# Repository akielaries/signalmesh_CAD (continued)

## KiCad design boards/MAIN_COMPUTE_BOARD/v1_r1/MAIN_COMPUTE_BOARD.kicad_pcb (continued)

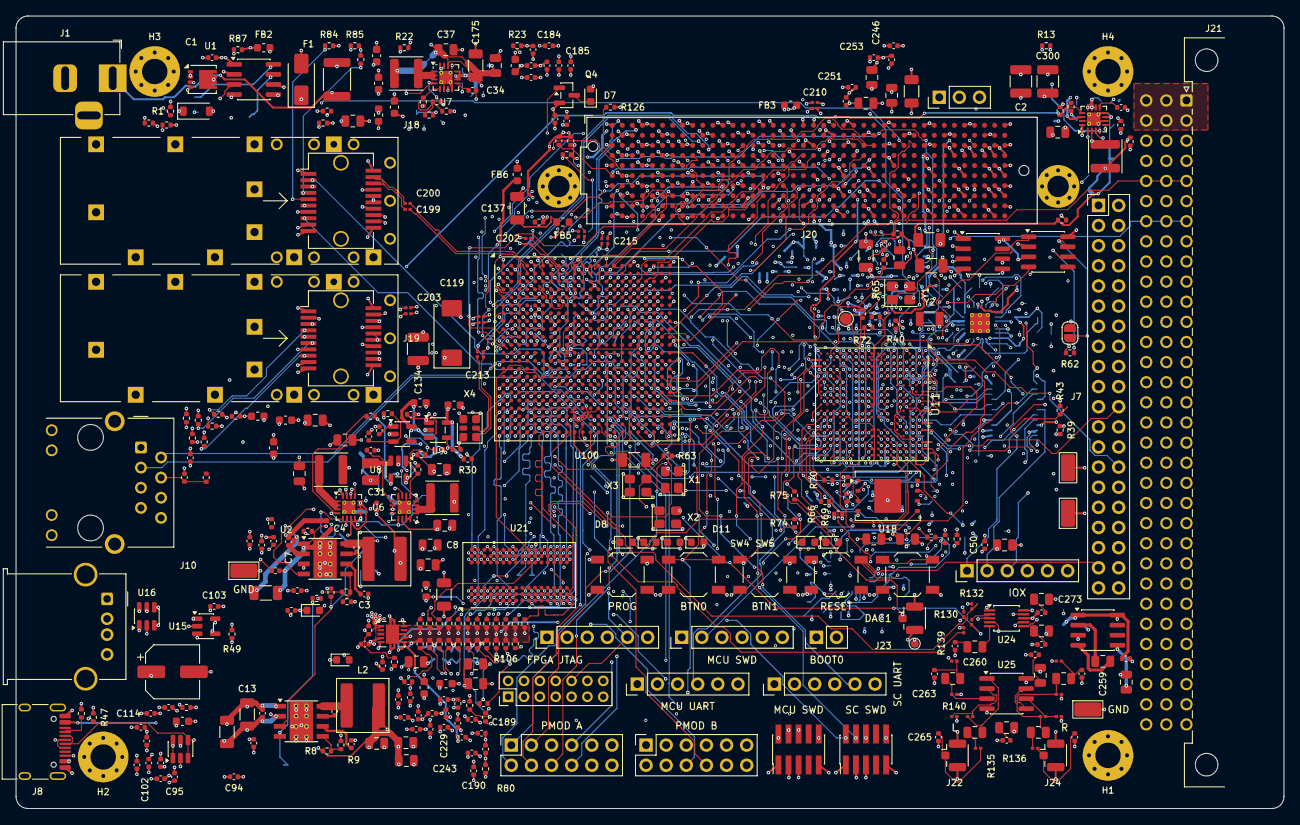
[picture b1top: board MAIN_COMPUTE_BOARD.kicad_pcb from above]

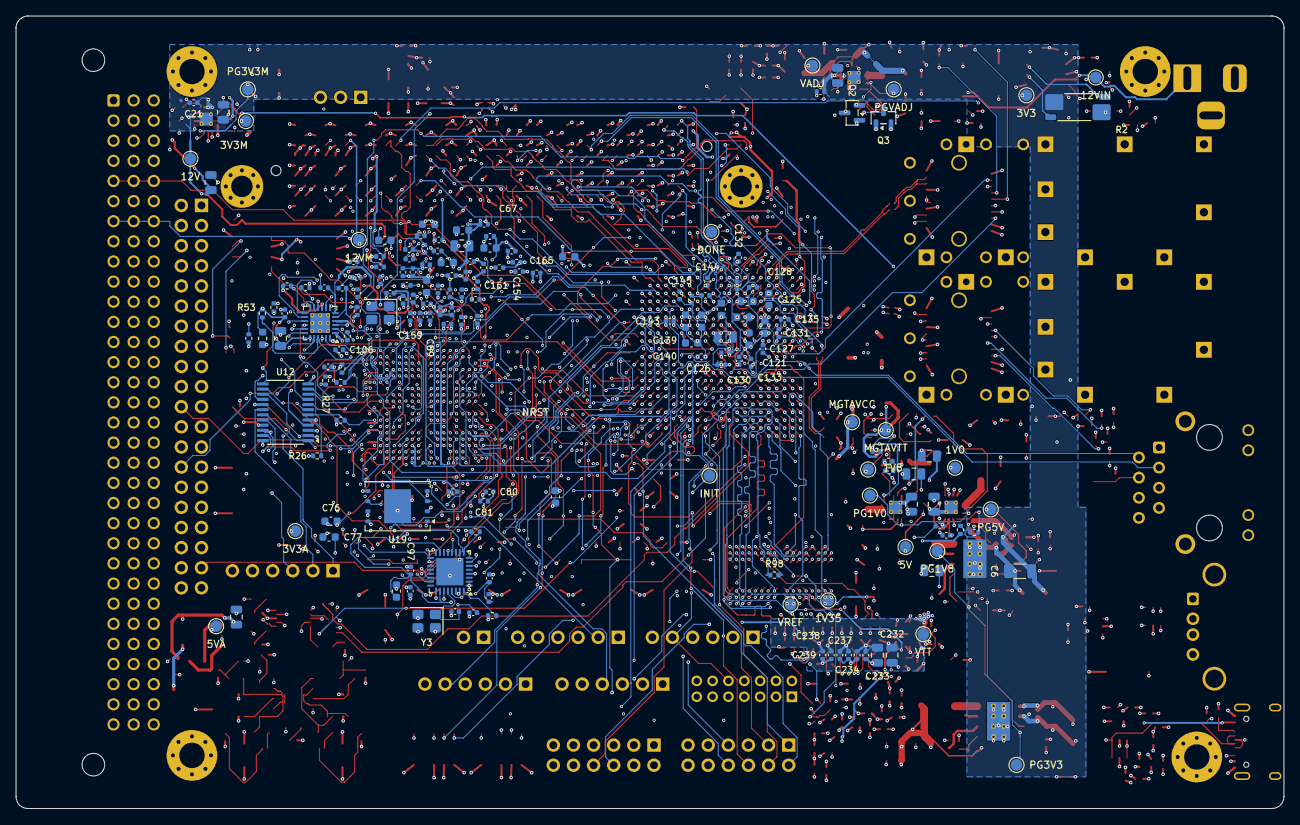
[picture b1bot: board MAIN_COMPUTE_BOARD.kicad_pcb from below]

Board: 10 copper layers, 160.0 x 100.0 mm, 547 parts (173 on the bottom side), 492 nets.

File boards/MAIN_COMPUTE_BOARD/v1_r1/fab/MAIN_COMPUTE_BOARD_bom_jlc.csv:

Comment,Designator,Footprint,LCSC Part #
100nF,"C1,C4,C12,C48,C50,C52-C72,C79,C81,C87-C89,C92-C95,C97,C98,C100,C110-C114,C116,C118,C148,C188-C190,C194,C195,C197,C198,C211,C217,C219,C222-C231,C234-C240,C242,C243,C246,C247,C250,C251",C_0402_1005Metric,
22uF 25V X5R,"C2,C300",C_1210_3225Metric,
1uF,"C3,C11,C42,C44,C45,C78,C80,C101-C103,C107,C115,C117,C241",C_0402_1005Metric,
10uF 25V,"C5,C6,C13,C14",C_1206_3216Metric,
100nF 25V,"C7,C15,C21,C26,C31,C36,C253",C_0402_1005Metric,
22uF,"C8-C10,C16-C18,C22,C23,C27,C28,C32,C33,C37,C38,C40,C41,C216,C218",C_0805_2012Metric,
3.3nF,"C19,C24,C29,C34",C_0402_1005Metric,
10uF 25V,"C20,C25,C30,C35,C51,C252",C_0805_2012Metric,
10uF,"C39,C47,C49,C75,C109,C147,C191,C192,C220,C221,C232,C233,C245,C249,C255-C260,C263,C266,C270,C273",C_0805_2012Metric,
4.7uF,"C43,C46,C73,C74,C96,C99,C120-C125,C138-C140,C150,C151,C156,C157,C162,C163,C169,C170,C176,C177,C182,C183,C193,C196",C_0603_1608Metric,
2.2uF,"C76,C77",C_0603_1608Metric,
10nF,C82,C_0402_1005Metric,
10pF,"C83,C84",C_0402_1005Metric,
8.2pF,"C85,C86",C_0402_1005Metric,
18pF,"C90,C91",C_0402_1005Metric,
100uF 10V,C104,CP_Elec_6.3x7.7,
15pF,"C105,C106",C_0402_1005Metric,
470pF,C108,C_0402_1005Metric,
330uF 2.5V polymer,C119,CP_EIA-7343-31_Kemet-D,
470nF,"C126-C133,C135,C136,C141-C145,C152-C155,C158-C161,C164-C167,C171-C174,C178-C181,C184-C187",C_0402_1005Metric,
100uF,C134,C_1210_3225Metric,
47uF,"C137,C146,C149,C168,C175,C244,C248",C_1206_3216Metric,
100nF,"C199-C210,C212-C215",C_0201_0603Metric,
0.1uF,"C254,C264,C268,C269,C272",C_0402_1005Metric,
2.7nF,"C261,C271",C_0402_1005Metric,
47pF,"C262,C265",C_0402_1005Metric,
100uF,C267,C_0805_2012Metric,
SMAJ15A,D1,D_SMA,
BZT52C10,D2,D_SOD-123,
RED 12V,D3,LED_0603_1608Metric,
GREEN 3V3,D4,LED_0603_1608Metric,
GREEN,"D5,D8-D11",LED_0603_1608Metric,
BLUE,D6,LED_0603_1608Metric,
GREEN DONE,D7,LED_0603_1608Metric,
3A hold 1812,F1,Fuse_1812_4532Metric,
1.1A hold 1206,F2,Fuse_1206_3216Metric,
600R@100MHz,FB1-FB8,L_0603_1608Metric,
12V IN 5.5x2.1,J1,BarrelJack_Horizontal,
BOOT0,J2,PinHeader_1x02_P2.54mm_Vertical,
MCU_SWD MIPI-10,J3,PinHeader_2x05_P1.27mm_Vertical_SMD,
MCU_SWD,J4,PinHeader_1x06_P2.54mm_Vertical,
MCU_UART FTDI,J5,PinHeader_1x06_P2.54mm_Vertical,
IOX_SPARE,J6,PinHeader_1x06_P2.54mm_Vertical,
MCU_BREAKOUT,J7,PinHeader_2x20_P2.54mm_Vertical,
USB-C HS,J8,USB_C_Receptacle_HRO_TYPE-C-31-M-12,
USB-A HOST MIDI,J9,USB_A_Molex_67643_Horizontal,
HR911105A,J10,RJ45_Hanrun_HR911105A_Horizontal,
CAN,J11,PinHeader_1x03_P2.54mm_Vertical,
FPGA_JTAG Xilinx,J12,PinHeader_2x07_P2.00mm_Vertical,
FPGA_JTAG 6p,J13,PinHeader_1x06_P2.54mm_Vertical,
SOFTCORE_SWD MIPI-10,J14,PinHeader_2x05_P1.27mm_Vertical_SMD,
SOFTCORE_UART FTDI,J15,PinHeader_1x06_P2.54mm_Vertical,
PMODA,J16,PinSocket_2x06_P2.54mm_Vertical,
PMODB,J17,PinSocket_2x06_P2.54mm_Vertical,
SFP cage,"J18,J19",Connector_SFP_and_Cage,
VITA57.1 HPC ASP-134486-01,J20,Samtec_FMC_ASP-134486-01_10x40_P1.27mm_Vertical,
DIN41612 C 3x32 BACKPLANE,J21,DIN41612_C_3x32_Male_Horizontal_THT,
ACM_DAC_L,J22,U.FL_Hirose_U.FL-R-SMT-1_Vertical,
DAC_L_PRB,J23,U.FL_Hirose_U.FL-R-SMT-1_Vertical,
ACM_DAC_R,J24,U.FL_Hirose_U.FL-R-SMT-1_Vertical,
6.8uH 6A,"L1,L2",L_Bourns_SRP6060FA,
2.2uH 4A,L3-L6,L_APV_ANR4020,
2.2uH 1.5A,L7,L_1008_2520Metric,
DMP3013SFV,Q1,Diodes_PowerDI3333-8,
2N7002,Q2-Q4,SOT-23,
10k,"R1,R22,R35,R37,R40,R43,R44,R48,R50-R53,R61,R72,R78-R80,R87,R88,R94,R95,R97,R124,R125",R_0402_1005Metric,
10m 1W,R2,R_Shunt_Vishay_WSK2512_6332Metric_T1.19mm,
100k,"R3,R5,R7,R8,R10,R12,R13,R16,R19,R23,R26,R27,R32,R49,R126",R_0402_1005Metric,
15k,R4,R_0402_1005Metric,
24.9k,R6,R_0402_1005Metric,
43.2k,R9,R_0402_1005Metric,
309k,R11,R_0402_1005Metric,
49.9k,R14,R_0402_1005Metric,
200k,"R15,R18,R21",R_0402_1005Metric,
249k,"R17,R20,R25",R_0402_1005Metric,
280k,R24,R_0402_1005Metric,
150k,R28,R_0402_1005Metric,
120k,R29,R_0402_1005Metric,
90.9k,R30,R_0402_1005Metric,
110k,"R31,R34",R_0402_1005Metric,
130k,R33,R_0402_1005Metric,
1k,"R36,R38,R39,R63-R65,R71,R73-R77",R_0402_1005Metric,
2.2k,"R41,R42",R_0402_1005Metric,
12k 1%,R45,R_0402_1005Metric,
5.1k,"R46,R47",R_0402_1005Metric,
1.5k,R54,R_0402_1005Metric,
12.1k 1%,R55,R_0402_1005Metric,
49.9 1%,R56-R59,R_0402_1005Metric,
0,R60,R_0402_1005Metric,
120,R62,R_0402_1005Metric,
4.7k,"R66,R67,R69,R70,R82-R86,R89-R93",R_0402_1005Metric,
330,R68,R_0402_1005Metric,
100 1%,"R81,R98",R_0402_1005Metric,
240 1%,R96,R_0402_1005Metric,
39.2 1%,R99-R121,R_0402_1005Metric,
10k 1%,"R122,R123",R_0402_1005Metric,
1k,"R127,R137",R_0201_0603Metric,
47k,"R128,R131",R_0201_0603Metric,
22,"R129,R130,R132,R138",R_0201_0603Metric,
2k,"R133,R140",R_0201_0603Metric,
560,"R134,R139",R_0201_0603Metric,
100,"R135,R136",R_0201_0603Metric,
MCU_RESET,SW1,SW_SPST_TL3342,
MCU_USER,SW2,SW_SPST_TL3342,
FPGA_PROG,SW3,SW_SPST_TL3342,
FPGA_BTN0,SW4,SW_SPST_TL3342,
FPGA_BTN1,SW5,SW_SPST_TL3342,
TP GND,TP21-TP24,TestPoint_Keystone_5015_Micro_Mini,
INA219 0x40,U1,SOIC-8_3.9x4.9mm_P1.27mm,
LMR33630ADDA,"U2,U3",Texas_HSOP-8-1EP_3.9x4.9mm_P1.27mm_ThermalVias,
TPS62130RGT,U4-U7,VQFN-16-1EP_3x3mm_P0.5mm_EP1.68x1.68mm_ThermalVias,
TLV62568DBV,U8,SOT-23-5,
TLV75801 MGTAVCC 1V0,U9,SOT-23-5,
TLV75801 MGTAVTT 1V2,U10,SOT-23-5,
STM32H755XIH6,U11,TFBGA-265_14x14mm_Layout17x17_P0.8mm,
TCA9535PWR 0x20,U12,TSSOP-24_4.4x7.8mm_P0.65mm,
USB3300-EZK,U13,QFN-32-1EP_5x5mm_P0.5mm_EP3.45x3.45mm,
USBLC6-2SC6,"U14,U16",SOT-23-6,
TPS2051C,U15,SOT-23-5,
LAN8742A-CZ,U17,VQFN-24-1EP_4x4mm_P0.5mm_EP2.5x2.5mm_ThermalVias,
W25Q01JVZEIQ,"U18,U19",WSON-8-1EP_8x6mm_P1.27mm_EP3.4x4.3mm,C6926235
SN65HVD230,U20,SOIC-8_3.9x4.9mm_P1.27mm,
MT41K256M16TW-107,U21,Micron_FBGA-96_8x14mm_Layout9x16_P0.8mm,
TPS51200DRC,U22,VSON-10-1EP_3x3mm_P0.5mm_EP1.65x2.4mm,
LM2662M,U23,SOIC-8_3.9x4.9mm_P1.27mm,
CS4344,U24,TSSOP-10_3x3mm_P0.5mm,
OPA1656ID,U25,SOIC-8_3.9x4.9mm_P1.27mm,
XC7A100T-2FGG484I,U100,Xilinx_FGG484,
24AA025E48 0x54 MAC,U200,SOIC-8_3.9x4.9mm_P1.27mm,
100MHz 3V3 CMOS,X1,Oscillator_SMD_Abracon_ASE-4Pin_3.2x2.5mm,
24.576MHz 3V3 CMOS,X2,Oscillator_SMD_Abracon_ASE-4Pin_3.2x2.5mm,
22.5792MHz 3V3 CMOS,X3,Oscillator_SMD_Abracon_ASE-4Pin_3.2x2.5mm,
125MHz LVDS,X4,Oscillator_SMD_SiTime_PQFD-6L_3.2x2.5mm,
25MHz 8pF,Y1,Crystal_SMD_3225-4Pin_3.2x2.5mm,
32.768kHz 6pF,Y2,Crystal_SMD_3215-2Pin_3.2x1.5mm,
24MHz 12pF,Y3,Crystal_SMD_3225-4Pin_3.2x2.5mm,
25MHz 10pF,Y4,Crystal_SMD_3225-4Pin_3.2x2.5mm,

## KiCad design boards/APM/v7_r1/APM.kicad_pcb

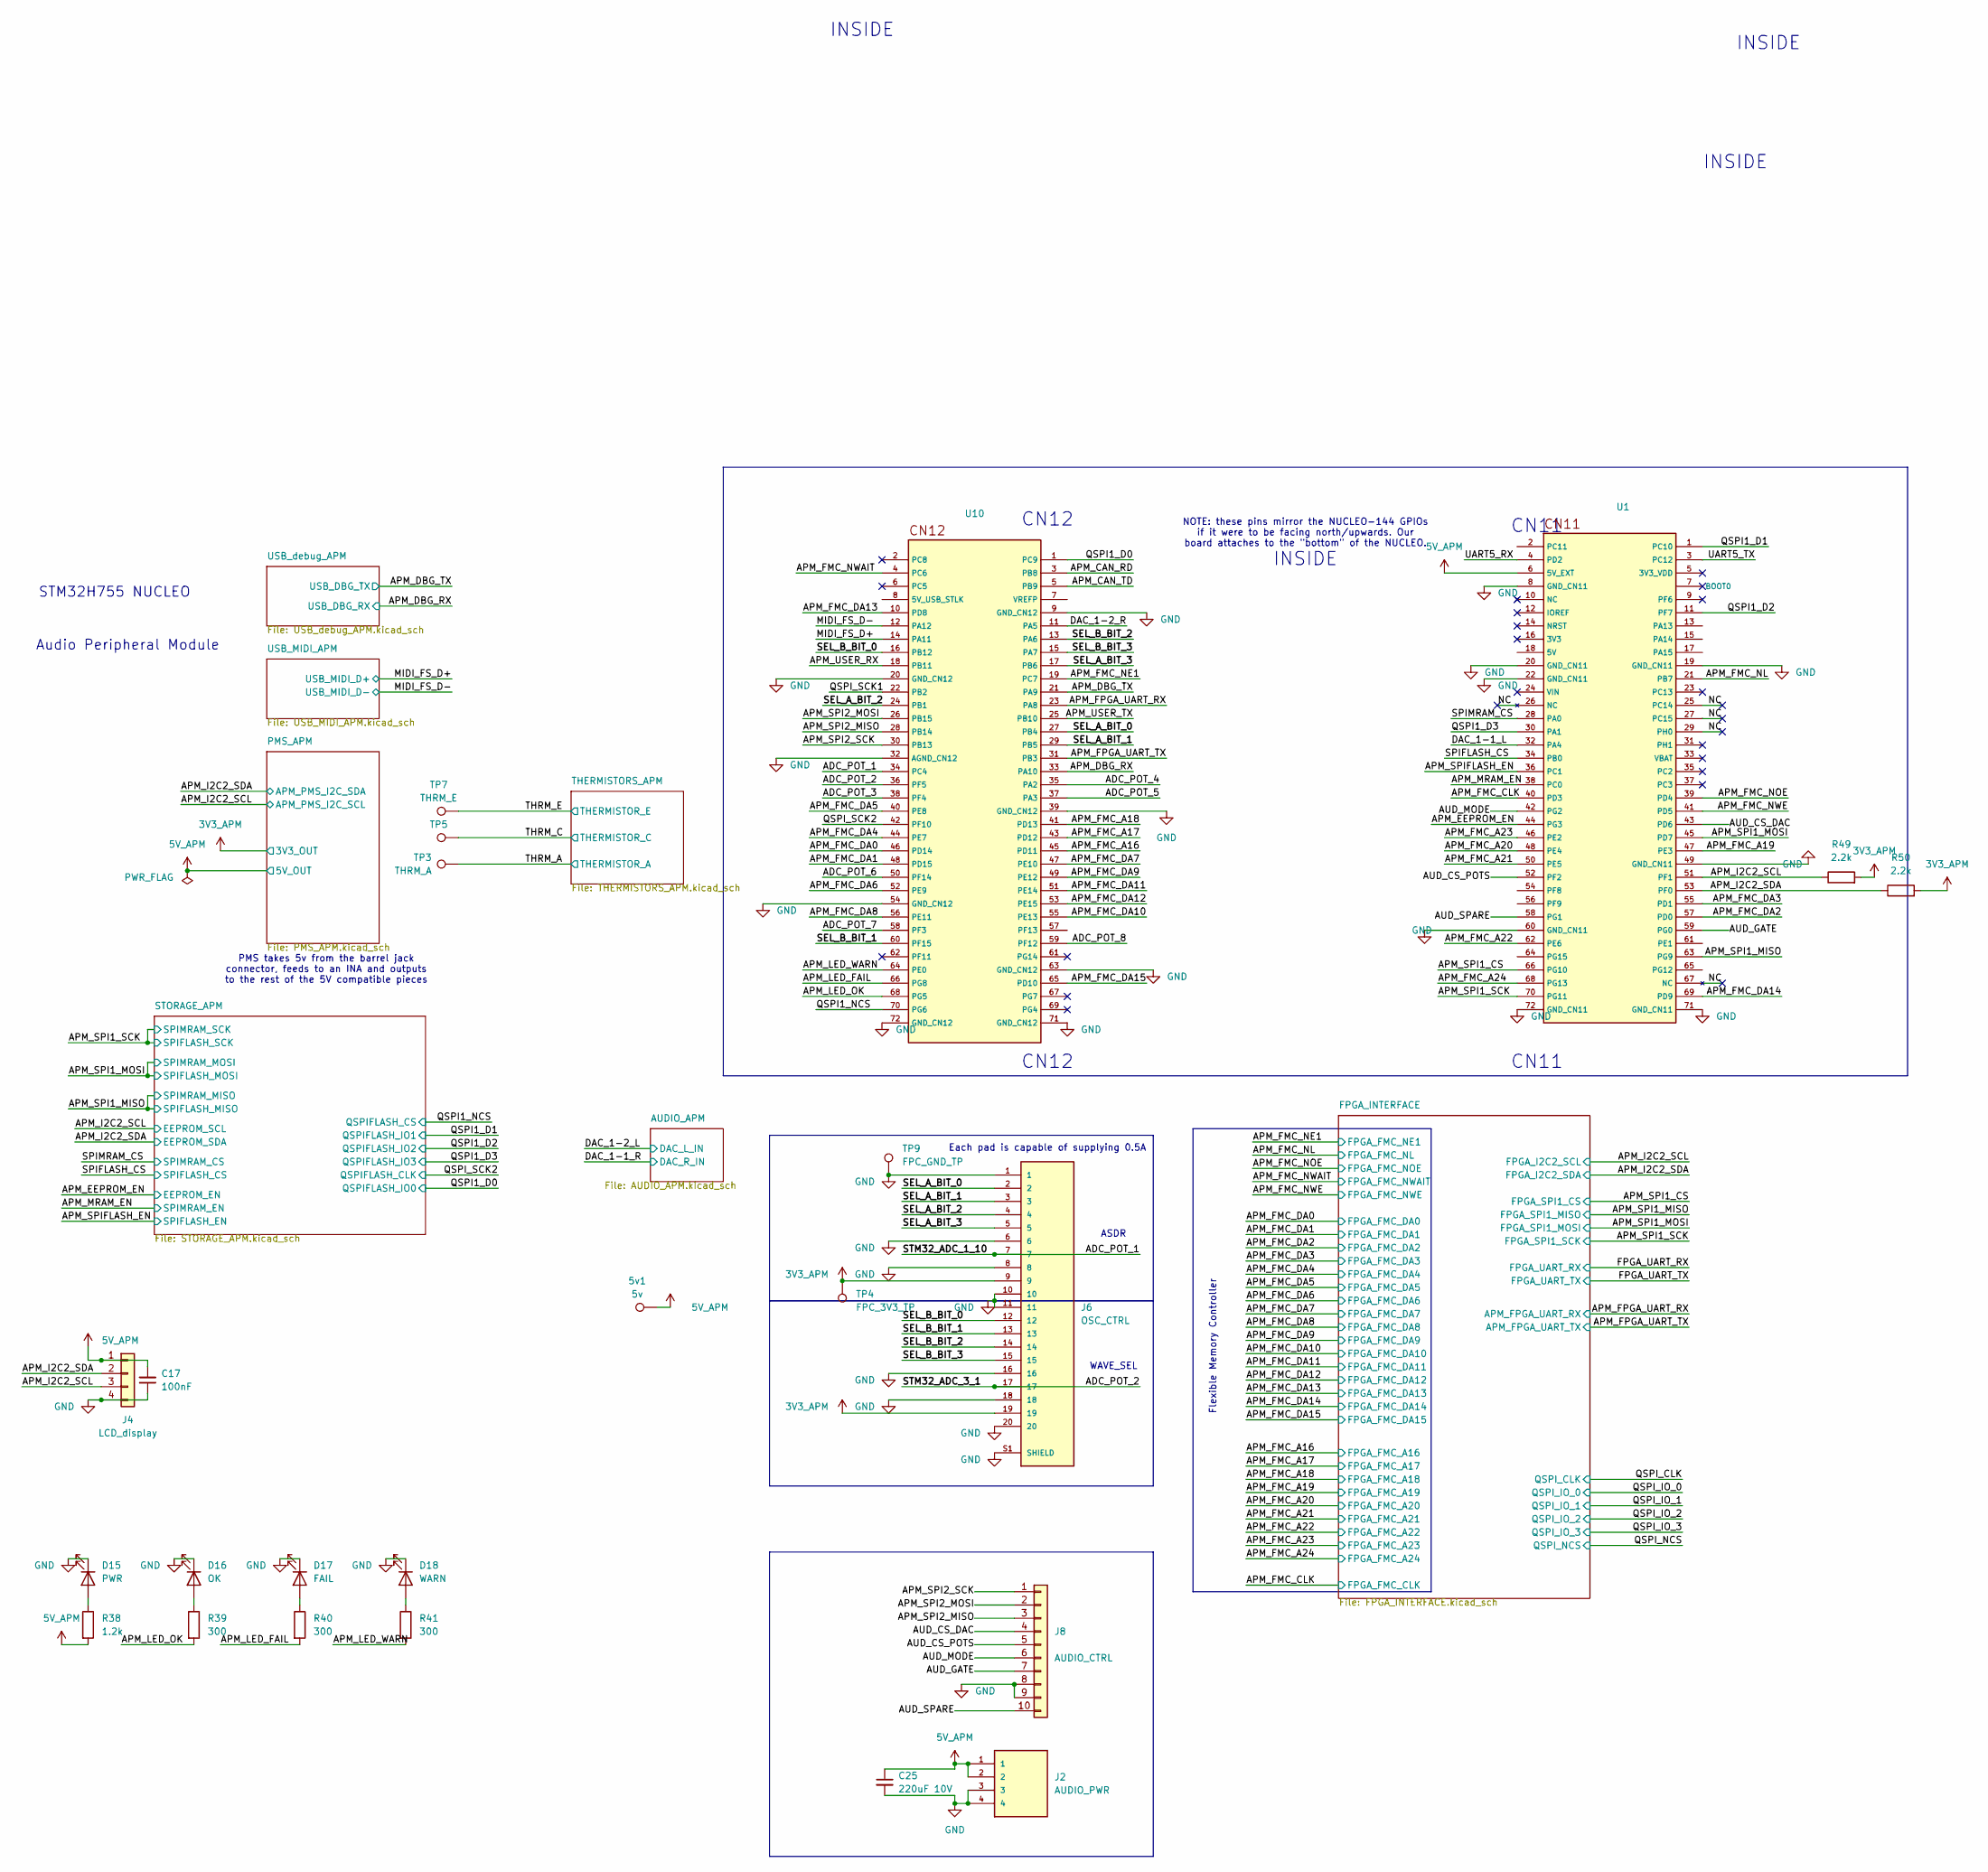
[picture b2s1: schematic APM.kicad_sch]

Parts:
5v1: 5v; TestPoint_Pad_D1.0mm
C17: 100nF; C_0805_2012Metric
C25: 220uF 10V; CP_Elec_4x3
D15: PWR; LED_0603_1608Metric
D16: OK; LED_0603_1608Metric
D17: FAIL; LED_0603_1608Metric
D18: WARN; LED_0603_1608Metric
J2: AUDIO_PWR; AMPHENOL_F3311A7H121004E200
J4: LCD_display; PinHeader_1x04_P2.54mm_Vertical_SMD_Pin1Left
J6: OSC_CTRL; GCT_FFC2B28-20-G; PARTREV A
J8: AUDIO_CTRL; Hirose_FH12-10S-0.5SH_1x10-1MP_P0.50mm_Horizontal
R38: 1.2k; R_0201_0603Metric; DigiKey_Part_Number 311-10.0KCRCT-ND
R39, R40, R41: 300; R_0201_0603Metric; DigiKey_Part_Number 311-10.0KCRCT-ND
R49, R50: 2.2k; R_0201_0603Metric; DigiKey_Part_Number 311-10.0KCRCT-ND
TP3: THRM_A; TestPoint_Pad_D1.0mm
TP4: FPC_3V3_TP; TestPoint_Pad_D1.0mm
TP5: THRM_C; TestPoint_Pad_D1.0mm
TP7: THRM_E; TestPoint_Pad_D1.0mm
TP9: FPC_GND_TP; TestPoint_Pad_D1.0mm
U1, U10: PinSocket_2x36_P2.54mm_Vertical

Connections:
3V3_APM: J6.9, J6.19, R49.2, R50.2, TP4.1 (1_1); also elsewhere on the board
5V_APM: 5v1.1 (1_1), C17.2, C25.1, J2.1, J2.2, J4.1, R38.2, U1.6 (5V_EXT); also elsewhere on the board
/ADC_POT_1: J6.7, U10.34 (PC4)
/ADC_POT_2: J6.17, U10.36 (PF5)
/ADC_POT_3: U10.38 (PF4)
/ADC_POT_4: U10.35 (PA2)
/ADC_POT_5: U10.37 (PA3)
/ADC_POT_6: U10.50 (PF14)
/ADC_POT_7: U10.58 (PF3)
/ADC_POT_8: U10.59 (PF12)
/APM_CAN_RD: U10.3 (PB8)
/APM_CAN_TD: U10.5 (PB9)
/APM_DBG_RX: U10.33 (PA10); also elsewhere on the board
/APM_DBG_TX: U10.21 (PA9); also elsewhere on the board
/APM_EEPROM_EN: U1.44 (PG3); also elsewhere on the board
/APM_FMC_A16: U10.45 (PD11); also elsewhere on the board
/APM_FMC_A17: U10.43 (PD12); also elsewhere on the board
/APM_FMC_A18: U10.41 (PD13); also elsewhere on the board
/APM_FMC_A19: U1.47 (PE3); also elsewhere on the board
/APM_FMC_A20: U1.48 (PE4); also elsewhere on the board
/APM_FMC_A21: U1.50 (PE5); also elsewhere on the board
/APM_FMC_A22: U1.62 (PE6); also elsewhere on the board
/APM_FMC_A23: U1.46 (PE2); also elsewhere on the board
/APM_FMC_A24: U1.68 (PG13); also elsewhere on the board
/APM_FMC_CLK: U1.40 (PD3); also elsewhere on the board
/APM_FMC_DA0: U10.46 (PD14); also elsewhere on the board
/APM_FMC_DA1: U10.48 (PD15); also elsewhere on the board
/APM_FMC_DA2: U1.57 (PD0); also elsewhere on the board
/APM_FMC_DA3: U1.55 (PD1); also elsewhere on the board
/APM_FMC_DA4: U10.44 (PE7); also elsewhere on the board
/APM_FMC_DA5: U10.40 (PE8); also elsewhere on the board
/APM_FMC_DA6: U10.52 (PE9); also elsewhere on the board
/APM_FMC_DA7: U10.47 (PE10); also elsewhere on the board
/APM_FMC_DA8: U10.56 (PE11); also elsewhere on the board
/APM_FMC_DA9: U10.49 (PE12); also elsewhere on the board
/APM_FMC_DA10: U10.55 (PE13); also elsewhere on the board
/APM_FMC_DA11: U10.51 (PE14); also elsewhere on the board
/APM_FMC_DA12: U10.53 (PE15); also elsewhere on the board
/APM_FMC_DA13: U10.10 (PD8); also elsewhere on the board
/APM_FMC_DA14: U1.69 (PD9); also elsewhere on the board
/APM_FMC_DA15: U10.65 (PD10); also elsewhere on the board
/APM_FMC_NE1: U10.19 (PC7); also elsewhere on the board
/APM_FMC_NL: U1.21 (PB7); also elsewhere on the board
/APM_FMC_NOE: U1.39 (PD4); also elsewhere on the board
/APM_FMC_NWAIT: U10.4 (PC6); also elsewhere on the board
/APM_FMC_NWE: U1.41 (PD5); also elsewhere on the board
/APM_FPGA_UART_RX: U10.23 (PA8); also elsewhere on the board
/APM_FPGA_UART_TX: U10.31 (PB3); also elsewhere on the board
/APM_I2C2_SCL: J4.3, R49.1, U1.51 (PF1); also elsewhere on the board
/APM_I2C2_SDA: J4.2, R50.1, U1.53 (PF0); also elsewhere on the board
/APM_LED_FAIL: R40.2, U10.66 (PG8)
/APM_LED_OK: R39.2, U10.68 (PG5)
/APM_LED_WARN: R41.2, U10.64 (PE0)
/APM_MRAM_EN: U1.38 (PC0); also elsewhere on the board
/APM_SPI1_CS: U1.66 (PG10); also elsewhere on the board
/APM_SPI1_MISO: U1.63 (PG9); also elsewhere on the board
/APM_SPI1_MOSI: U1.45 (PD7); also elsewhere on the board
/APM_SPI1_SCK: U1.70 (PG11); also elsewhere on the board
/APM_SPI2_MISO: J8.3, U10.28 (PB14)
/APM_SPI2_MOSI: J8.2, U10.26 (PB15)
/APM_SPI2_SCK: J8.1, U10.30 (PB13)
/APM_SPIFLASH_EN: U1.36 (PC1); also elsewhere on the board
/APM_USER_RX: U10.18 (PB11)
/APM_USER_TX: U10.25 (PB10)
/AUD_CS_DAC: J8.4, U1.43 (PD6)
/AUD_CS_POTS: J8.5, U1.52 (PF2)
/AUD_GATE: J8.7, U1.59 (PG0)
/AUD_MODE: J8.6, U1.42 (PG2)
/AUD_SPARE: J8.10, U1.58 (PG1)
/DAC_1-1_L: U1.32 (PA4)
/DAC_1-2_R: U10.11 (PA5)
/MIDI_FS_D+: U10.14 (PA11); also elsewhere on the board
/MIDI_FS_D-: U10.12 (PA12); also elsewhere on the board
/NC: U1.25 (PC14), U1.26 (NC), U1.27 (PC15), U1.29 (PH0), U1.67 (NC)
/QSPI1_D0: U10.1 (PC9); also elsewhere on the board
/QSPI1_D1: U1.1 (PC10); also elsewhere on the board
/QSPI1_D2: U1.11 (PF7); also elsewhere on the board
/QSPI1_D3: U1.30 (PA1); also elsewhere on the board
/QSPI1_NCS: U10.70 (PG6); also elsewhere on the board
/QSPI_SCK1: U10.22 (PB2)
/QSPI_SCK2: U10.42 (PF10); also elsewhere on the board
/SEL_A_BIT_0: J6.2, U10.27 (PB4)
/SEL_A_BIT_1: J6.3, U10.29 (PB5)
/SEL_A_BIT_2: J6.4, U10.24 (PB1)
/SEL_A_BIT_3: J6.5, U10.17 (PB6)
/SEL_B_BIT_0: J6.12, U10.16 (PB12)
/SEL_B_BIT_1: J6.13, U10.60 (PF15)
/SEL_B_BIT_2: J6.14, U10.13 (PA6)
/SEL_B_BIT_3: J6.15, U10.15 (PA7)
/SPIFLASH_CS: U1.34 (PB0); also elsewhere on the board
/SPIMRAM_CS: U1.28 (PA0); also elsewhere on the board
/UART5_RX: U1.4 (PD2)
/UART5_TX: U1.3 (PC12)
GND: C17.1, C25.2, D15.1 (K), D16.1 (K), D17.1 (K), D18.1 (K), J2.3, J2.4, J4.4, J6.1, J6.6, J6.8, J6.10, J6.11, J6.16, J6.18, J6.20, J6.S1 (SHIELD), J6.S2 (SHIELD), J8.8, J8.9, TP9.1 (1_1), U1.8 (GND_CN11), U1.19 (GND_CN11), U1.20 (GND_CN11), U1.22 (GND_CN11), U1.49 (GND_CN11), U1.60 (GND_CN11), U1.71 (GND_CN11), U1.72 (GND_CN11), U10.9 (GND_CN12), U10.20 (GND_CN12), U10.32 (AGND_CN12), U10.39 (GND_CN12), U10.54 (GND_CN12), U10.63 (GND_CN12), U10.71 (GND_CN12), U10.72 (GND_CN12); also elsewhere on the board
unnamed: D15.2 (A), R38.1
unnamed: D16.2 (A), R39.1
unnamed: D17.2 (A), R40.1
unnamed: D18.2 (A), R41.1

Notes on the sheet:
WAVE_SEL
STM32H755 NUCLEO
CN12
PMS takes 5v from the barrel jack connector, feeds to an INA and outputs to the rest of the 5V compatible pieces
INSIDE
Flexible Memory Controller
Audio Peripheral Module
NOTE: these pins mirror the NUCLEO-144 GPIOs if it were to be facing north/upwards. Our board attaches to the "bottom" of the NUCLEO.
Each pad is capable of supplying 0.5A
ASDR
CN11

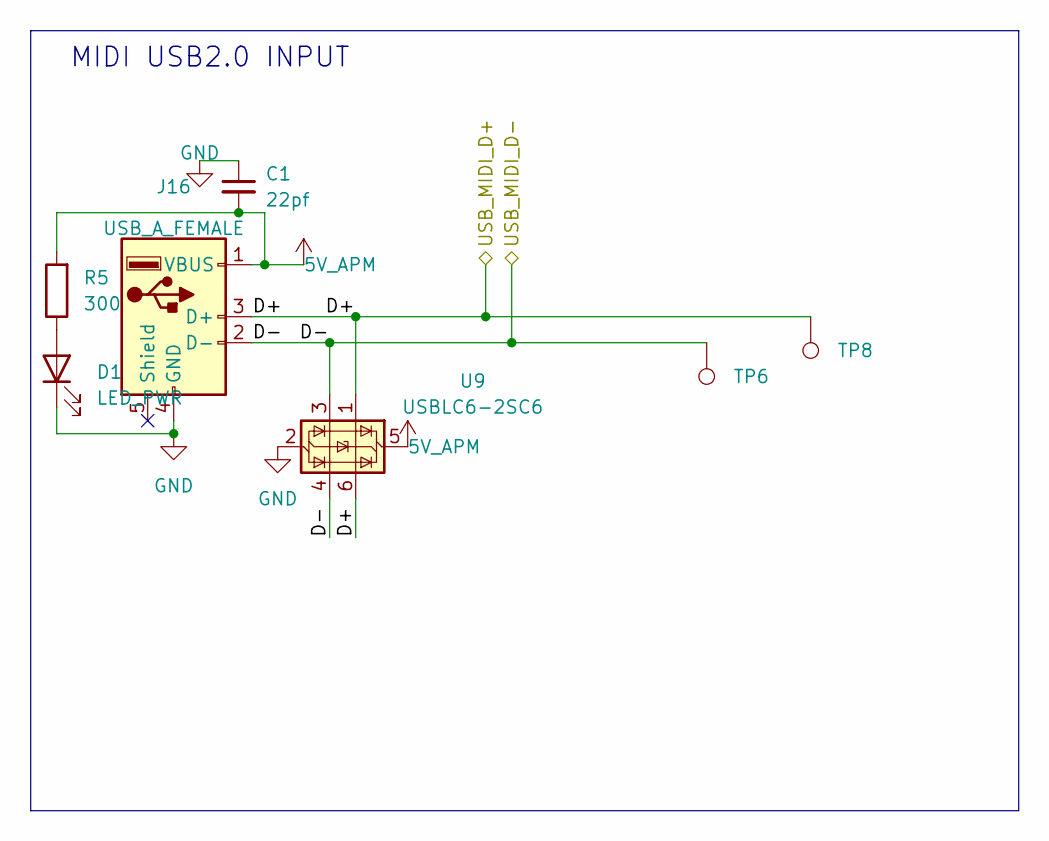
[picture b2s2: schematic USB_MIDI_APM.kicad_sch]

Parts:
C1: 22pf; C_0805_2012Metric
D1: LED_PWR; LED_0603_1608Metric
J16: USB_A_FEMALE; USB_A_Molex_67643_Horizontal
R5: 300; R_0201_0603Metric; DigiKey_Part_Number 311-10.0KCRCT-ND
TP6: MIDI_D-; TestPoint_Pad_D1.0mm
TP8: MIDI_D+; TestPoint_Pad_D1.0mm
U9: USBLC6-2SC6; SOT-23-6

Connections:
5V_APM: C1.2, J16.1 (VBUS), R5.2, U9.5 (VBUS); also elsewhere on the board
/MIDI_FS_D+: J16.3 (D+), TP8.1 (1_1), U9.1 (I/O1), U9.6 (I/O1); also elsewhere on the board
/MIDI_FS_D-: J16.2 (D-), TP6.1 (1_1), U9.3 (I/O2), U9.4 (I/O2); also elsewhere on the board
GND: C1.1, D1.1 (K), J16.4 (GND), U9.2 (GND); also elsewhere on the board
unnamed: D1.2 (A), R5.1

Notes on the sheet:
MIDI USB2.0 INPUT

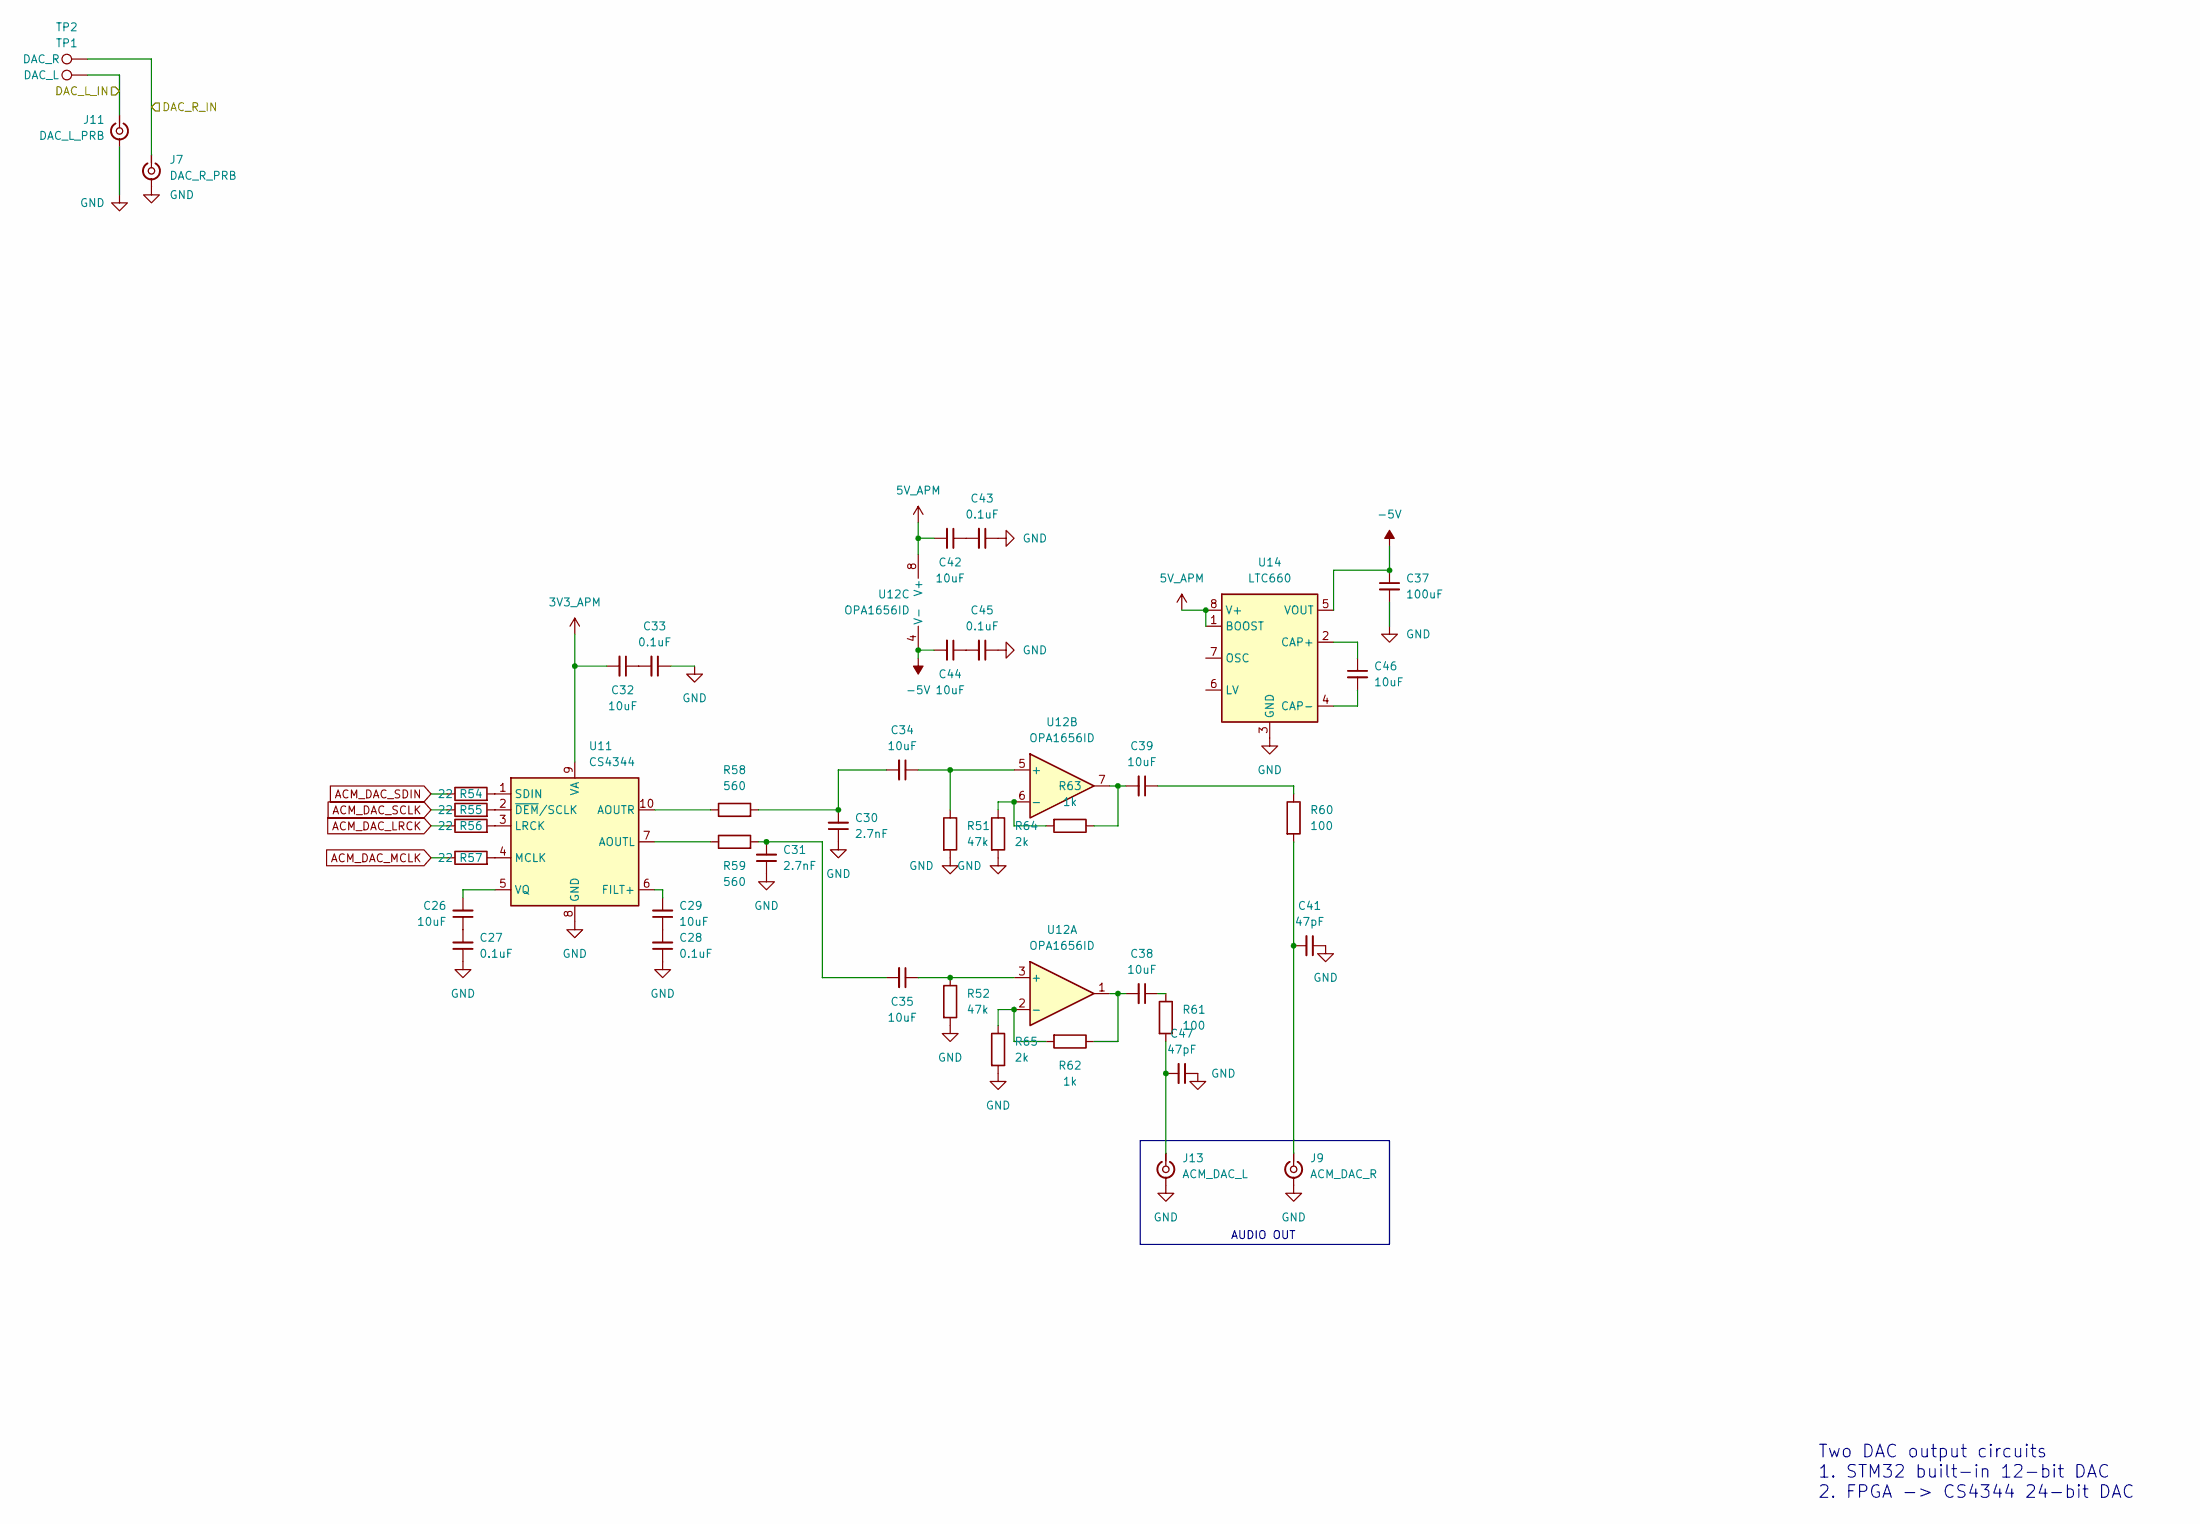
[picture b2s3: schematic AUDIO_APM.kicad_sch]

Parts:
C26, C29, C32, C34, C35, C38, C39, C42, C44, C46: 10uF; C_0805_2012Metric
C27, C28, C33, C43, C45: 0.1uF; C_0402_1005Metric
C30, C31: 2.7nF; C_0402_1005Metric
C37: 100uF; C_0805_2012Metric
C41, C47: 47pF; C_0402_1005Metric
J7: DAC_R_PRB; U.FL_Hirose_U.FL-R-SMT-1_Vertical
J9: ACM_DAC_R; U.FL_Hirose_U.FL-R-SMT-1_Vertical
J11: DAC_L_PRB; U.FL_Hirose_U.FL-R-SMT-1_Vertical
J13: ACM_DAC_L; U.FL_Hirose_U.FL-R-SMT-1_Vertical
R51, R52: 47k; R_0201_0603Metric; DigiKey_Part_Number 311-10.0KCRCT-ND
R54, R55, R56, R57: 22; R_0201_0603Metric; DigiKey_Part_Number 311-10.0KCRCT-ND
R58, R59: 560; R_0201_0603Metric; DigiKey_Part_Number 311-10.0KCRCT-ND
R60, R61: 100; R_0201_0603Metric; DigiKey_Part_Number 311-10.0KCRCT-ND
R62, R63: 1k; R_0201_0603Metric; DigiKey_Part_Number 311-10.0KCRCT-ND
R64, R65: 2k; R_0201_0603Metric; DigiKey_Part_Number 311-10.0KCRCT-ND
TP1: DAC_L; TestPoint_Pad_D1.0mm
TP2: DAC_R; TestPoint_Pad_D1.0mm
U11: CS4344; TSSOP-10_3x3mm_P0.5mm
U12: OPA1656ID; SOIC-8_3.9x4.9mm_P1.27mm
U14: LTC660; SOIC-8_3.9x4.9mm_P1.27mm

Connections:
3V3_APM: C32.2, U11.9 (VA); also elsewhere on the board
5V_APM: C42.2, U12.8 (V+), U14.1 (BOOST), U14.8 (V+); also elsewhere on the board
-5V: C37.1, C44.2, U12.4 (V-), U14.5 (VOUT)
/DAC_1-1_R: J7.1 (In), TP2.1 (1_1)
/DAC_1-2_L: J11.1 (In), TP1.1 (1_1)
ACM_DAC_LRCK: R56.1; also elsewhere on the board
ACM_DAC_MCLK: R57.1; also elsewhere on the board
ACM_DAC_SCLK: R55.1; also elsewhere on the board
ACM_DAC_SDIN: R54.1; also elsewhere on the board
GND: C27.1, C28.1, C30.1, C31.1, C33.1, C37.2, C41.1, C43.1, C45.1, C47.1, J7.2 (Ext), J9.2 (Ext), J11.2 (Ext), J13.2 (Ext), R51.2, R52.2, R64.2, R65.2, U11.8 (GND), U14.3 (GND); also elsewhere on the board
unnamed: C26.1, C27.2
unnamed: C28.2, C29.1
unnamed: C30.2, C34.2, R58.2
unnamed: C31.2, C35.2, R59.2
unnamed: C32.1, C33.2
unnamed: C38.1, R61.1
unnamed: C38.2, R62.1, U12.1
unnamed: C39.1, R60.1
unnamed: C39.2, R63.1, U12.7
unnamed: C42.1, C43.2
unnamed: C44.1, C45.2
unnamed: C41.2, J9.1 (In), R60.2
unnamed: C47.2, J13.1 (In), R61.2
unnamed: R59.1, U11.7 (AOUTL)
unnamed: R58.1, U11.10 (AOUTR)
unnamed: C29.2, U11.6 (FILT+)
unnamed: R56.2, U11.3 (LRCK)
unnamed: R57.2, U11.4 (MCLK)
unnamed: R54.2, U11.1 (SDIN)
unnamed: C26.2, U11.5 (VQ)
unnamed: R55.2, U11.2 (~DEM/SCLK)
unnamed: C35.1, R52.1, U12.3 (+)
unnamed: R62.2, R65.1, U12.2 (-)
unnamed: C34.1, R51.1, U12.5 (+)
unnamed: R63.2, R64.1, U12.6 (-)
unnamed: C46.1, U14.2 (CAP+)
unnamed: C46.2, U14.4 (CAP-)

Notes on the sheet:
AUDIO OUT
Two DAC output circuits 1. STM32 built-in 12-bit DAC 2. FPGA -> CS4344 24-bit DAC

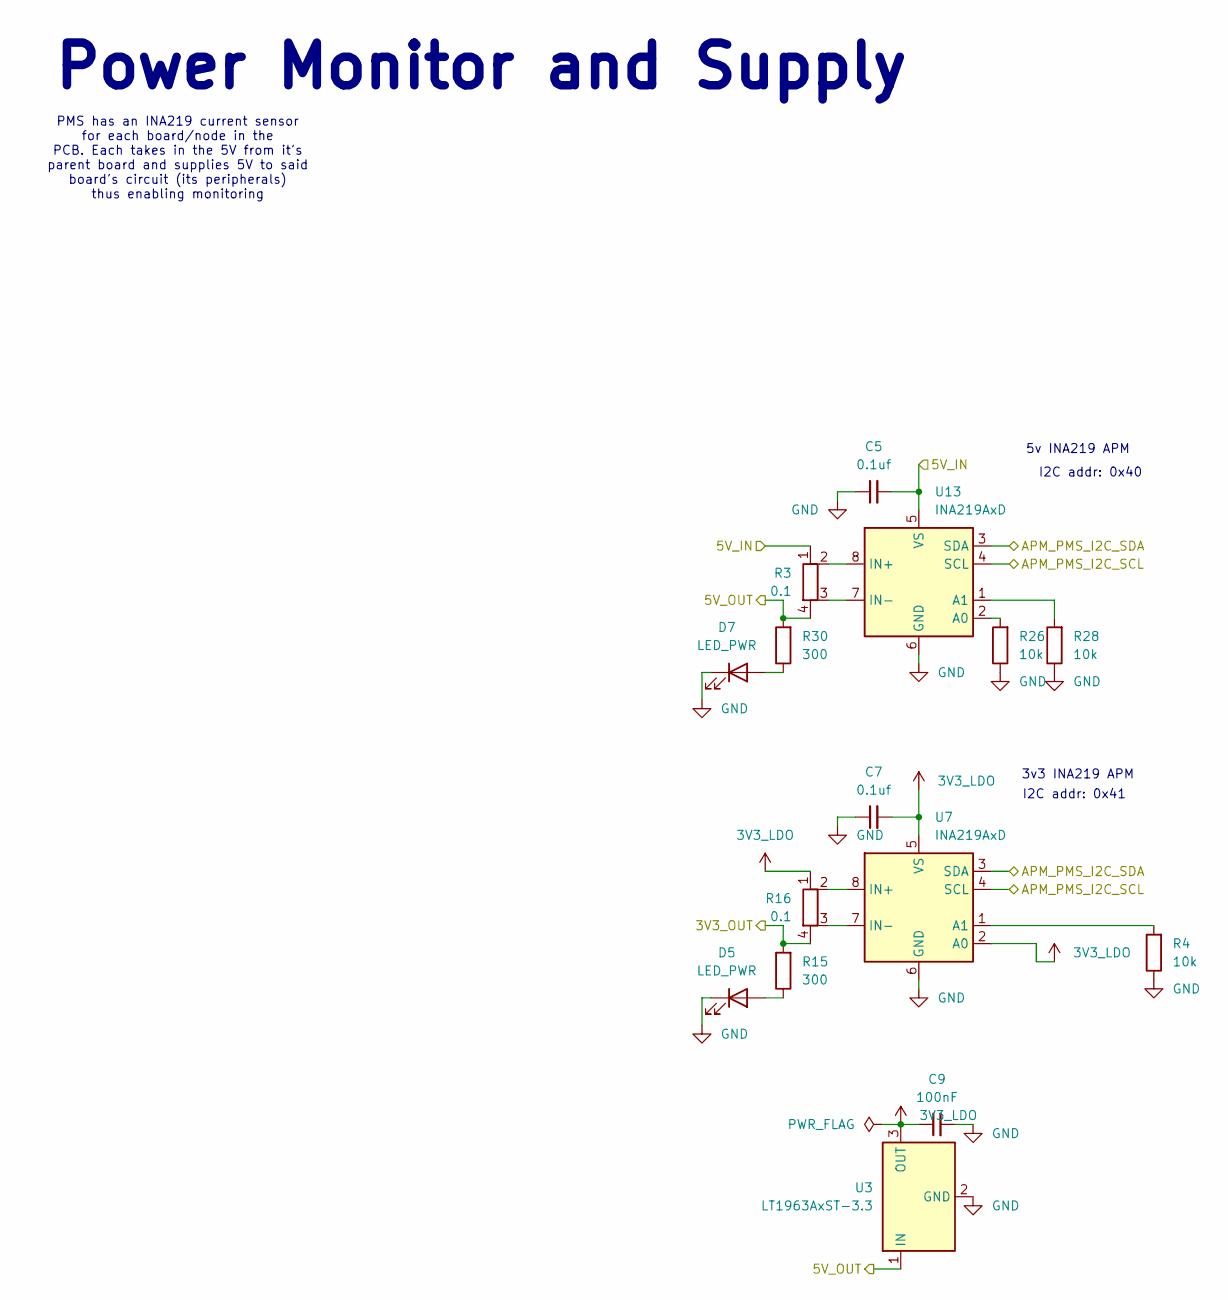
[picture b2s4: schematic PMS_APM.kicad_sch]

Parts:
C5, C7: 0.1uf; C_0805_2012Metric
C9: 100nF; C_0805_2012Metric
D5, D7: LED_PWR; LED_0603_1608Metric
R3, R16: 0.1; R_Shunt_Ohmite_LVK12
R4, R26, R28: 10k; R_0201_0603Metric; DigiKey_Part_Number 311-10.0KCRCT-ND
R15, R30: 300; R_0201_0603Metric; DigiKey_Part_Number 311-10.0KCRCT-ND
U3: LT1963AxST-3.3; SOT-223-3_TabPin2
U7, U13: INA219AxD; SOIC-8_3.9x4.9mm_P1.27mm

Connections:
3V3_APM: R15.2, R16.4; also elsewhere on the board
5V_APM: R3.4, R30.2, U3.1 (IN); also elsewhere on the board
/APM_I2C2_SCL: U7.4 (SCL), U13.4 (SCL); also elsewhere on the board
/APM_I2C2_SDA: U7.3 (SDA), U13.3 (SDA); also elsewhere on the board
GND: C5.1, C7.1, C9.2, D5.1 (K), D7.1 (K), R4.1, R26.1, R28.1, U3.2 (GND), U7.6 (GND), U13.6 (GND); also elsewhere on the board
unnamed: D5.2 (A), R15.1
unnamed: D7.2 (A), R30.1
unnamed: R4.2, U7.1 (A1)
unnamed: R16.2, U7.8 (IN+)
unnamed: R16.3, U7.7 (IN-)
unnamed: R26.2, U13.2 (A0)
unnamed: R28.2, U13.1 (A1)
unnamed: R3.2, U13.8 (IN+)
unnamed: R3.3, U13.7 (IN-)

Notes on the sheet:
I2C addr: 0x40
Power Monitor and Supply
3v3 INA219 APM
PMS has an INA219 current sensor for each board/node in the PCB. Each takes in the 5V from it's parent board and supplies 5V to said board's circuit (its peripherals) thus enabling monitoring
I2C addr: 0x41
5v INA219 APM
